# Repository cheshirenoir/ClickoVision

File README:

ClickoVision
A controller replacement for the colecovision.
CC BY SA
See https://ilike8bits.com/introducing-the-clickovision-a-replacement-controller-for-the-colecovision/ for build details and parts.

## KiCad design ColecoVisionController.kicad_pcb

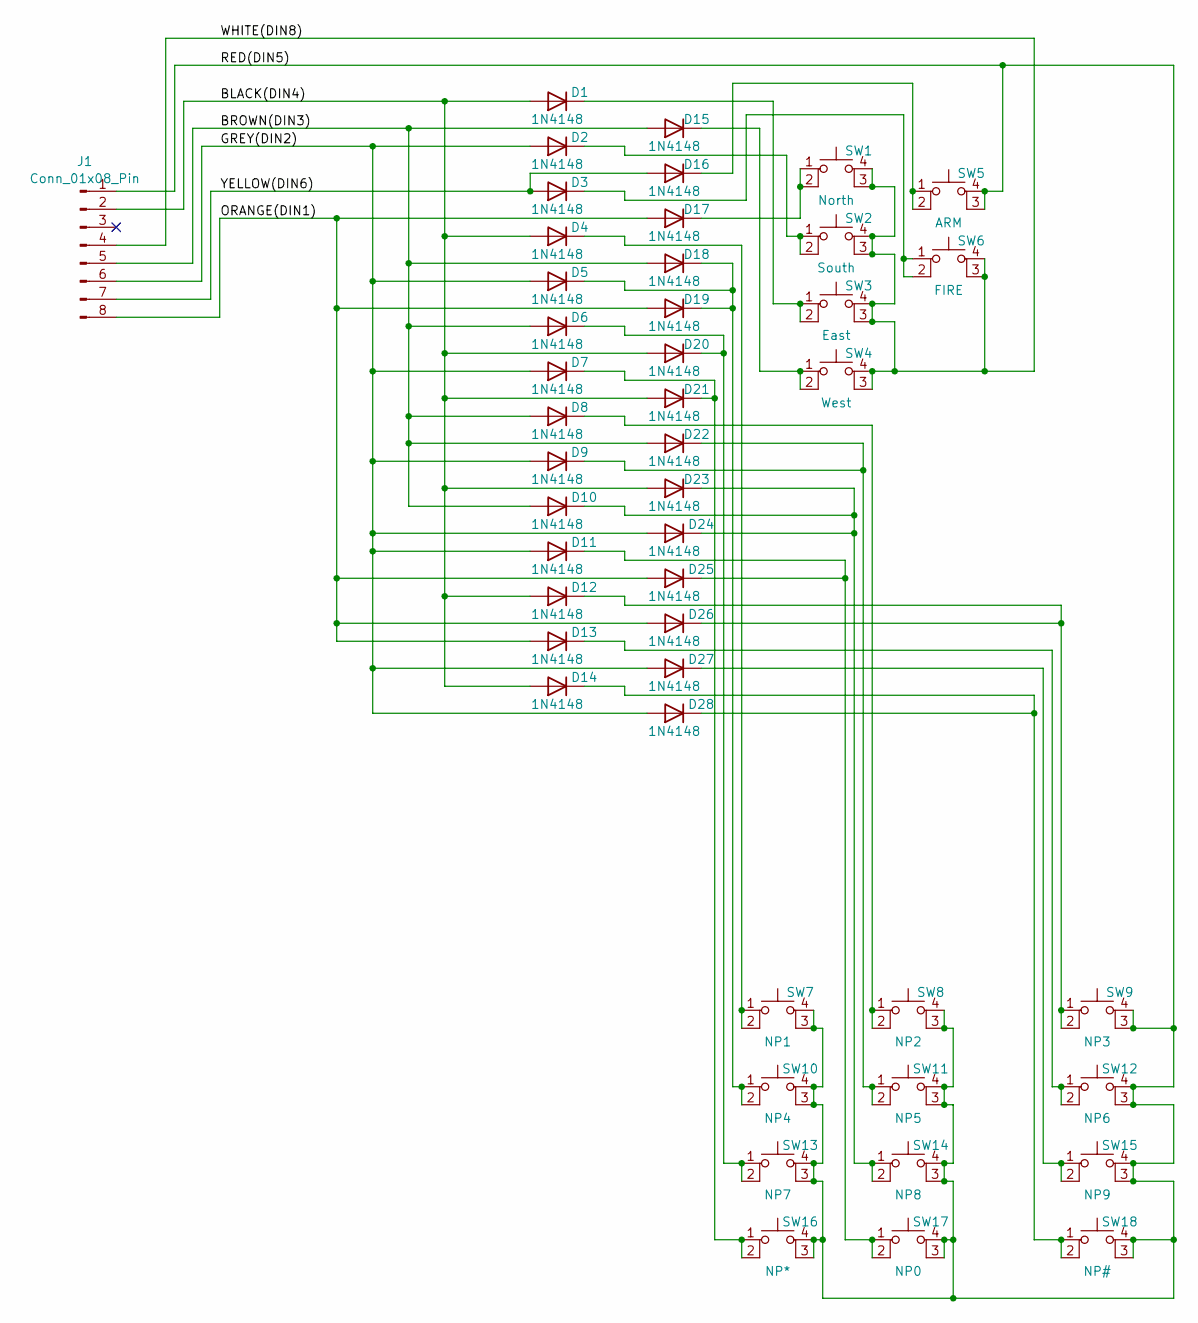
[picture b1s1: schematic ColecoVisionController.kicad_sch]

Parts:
D1, D2, D3, D4, D5, D6, D7, D8, D9, D10, D11, D12, D13, D14, D15, D16, D17, D18, D19, D20, D21, D22, D23, D24, D25, D26, D27, D28: 1N4148; D_MiniMELF_Handsoldering
J1: Conn_01x08_Pin; PinHeader_1x08_P2.54mm_Horizontal
SW1: North; DPadSwitch
SW2: South; DPadSwitch
SW3: East; DPadSwitch
SW4: West; DPadSwitch
SW5: ARM; SnapActionSwitch
SW6: FIRE; SnapActionSwitch
SW7: NP1; SW_PUSH_4pin_6mm
SW8: NP2; SW_PUSH_4pin_6mm
SW9: NP3; SW_PUSH_4pin_6mm
SW10: NP4; SW_PUSH_4pin_6mm
SW11: NP5; SW_PUSH_4pin_6mm
SW12: NP6; SW_PUSH_4pin_6mm
SW13: NP7; SW_PUSH_4pin_6mm
SW14: NP8; SW_PUSH_4pin_6mm
SW15: NP9; SW_PUSH_4pin_6mm
SW16: NP*; SW_PUSH_4pin_6mm
SW17: NP0; SW_PUSH_4pin_6mm
SW18: NP#; SW_PUSH_4pin_6mm

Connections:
/BLACK(DIN4): D1.2 (A), D4.2 (A), D12.2 (A), D14.2 (A), D20.2 (A), D21.2 (A), D23.2 (A), J1.2
/BROWN(DIN3): D6.2 (A), D8.2 (A), D10.2 (A), D15.2 (A), D18.2 (A), D22.2 (A), J1.5
/GREY(DIN2): D2.2 (A), D5.2 (A), D7.2 (A), D9.2 (A), D11.2 (A), D24.2 (A), D27.2 (A), D28.2 (A), J1.6
/ORANGE(DIN1): D13.2 (A), D17.2 (A), D19.2 (A), D25.2 (A), D26.2 (A), J1.8
/RED(DIN5): J1.1, SW5.3 (K), SW5.4 (A), SW7.3 (K), SW7.4 (A), SW8.3 (K), SW8.4 (A), SW9.3 (K), SW9.4 (A), SW10.3 (K), SW10.4 (A), SW11.3 (K), SW11.4 (A), SW12.3 (K), SW12.4 (A), SW13.3 (K), SW13.4 (A), SW14.3 (K), SW14.4 (A), SW15.3 (K), SW15.4 (A), SW16.3 (K), SW16.4 (A), SW17.3 (K), SW17.4 (A), SW18.3 (K), SW18.4 (A)
/WHITE(DIN8): J1.4, SW1.3 (K), SW1.4 (A), SW2.3 (K), SW2.4 (A), SW3.3 (K), SW3.4 (A), SW4.3 (K), SW4.4 (A), SW6.3 (K), SW6.4 (A)
/YELLOW(DIN6): D3.2 (A), D16.2 (A), J1.7
unnamed: D1.1 (K), SW3.1, SW3.2
unnamed: D2.1 (K), SW2.1, SW2.2
unnamed: D3.1 (K), SW6.1, SW6.2
unnamed: D4.1 (K), SW7.1, SW7.2
unnamed: D8.1 (K), SW8.1, SW8.2
unnamed: D10.1 (K), D23.1 (K), D24.1 (K), SW14.1, SW14.2
unnamed: D11.1 (K), D25.1 (K), SW17.1, SW17.2
unnamed: D12.1 (K), D26.1 (K), SW9.1, SW9.2
unnamed: D13.1 (K), SW12.1, SW12.2
unnamed: D14.1 (K), D28.1 (K), SW18.1, SW18.2
unnamed: D15.1 (K), SW4.1, SW4.2
unnamed: D16.1 (K), SW5.1, SW5.2
unnamed: D17.1 (K), SW1.1, SW1.2
unnamed: D5.1 (K), D18.1 (K), D19.1 (K), SW10.1, SW10.2
unnamed: D6.1 (K), D20.1 (K), SW13.1, SW13.2
unnamed: D7.1 (K), D21.1 (K), SW16.1, SW16.2
unnamed: D9.1 (K), D22.1 (K), SW11.1, SW11.2
unnamed: D27.1 (K), SW15.1, SW15.2

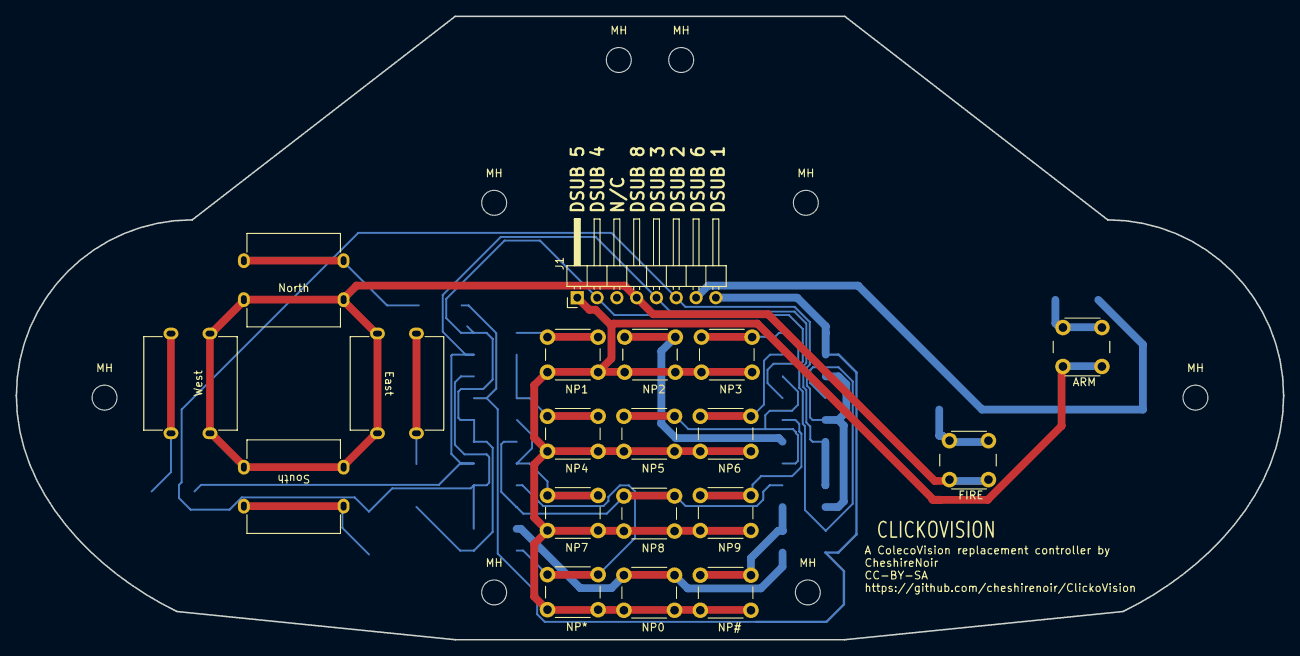
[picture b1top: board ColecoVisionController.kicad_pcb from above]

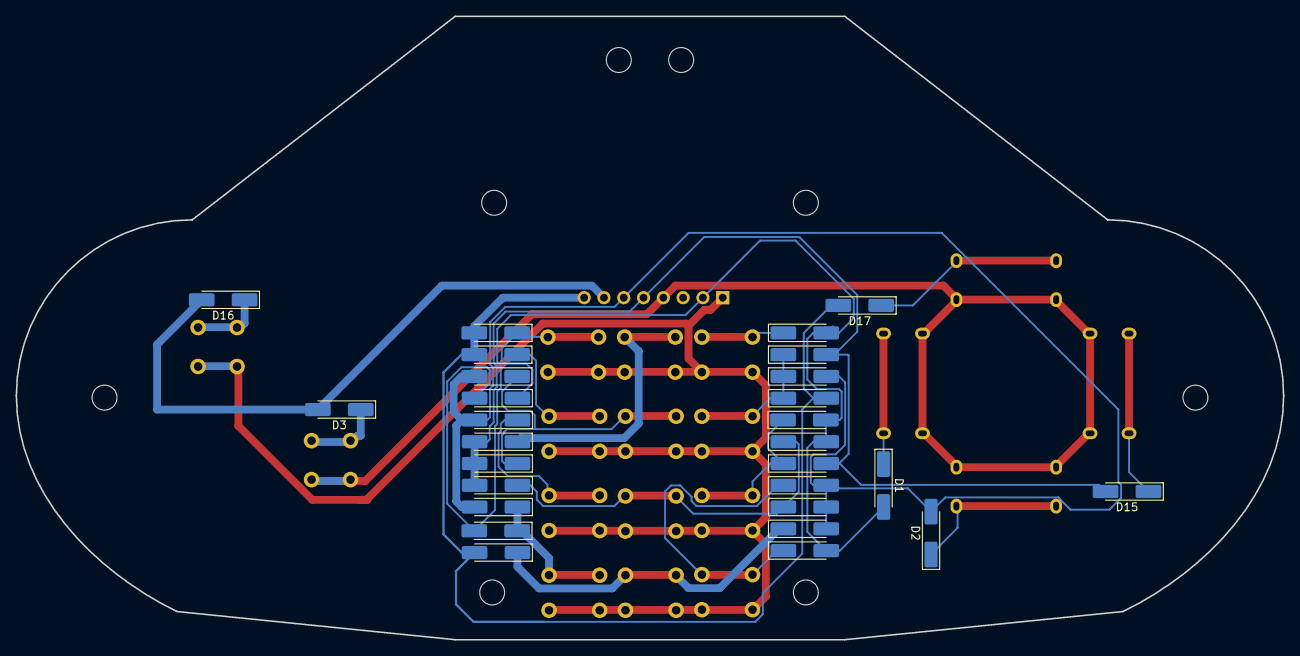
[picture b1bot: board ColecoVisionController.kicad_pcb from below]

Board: 2 copper layers, 162.6 x 80.0 mm, 55 parts (28 on the bottom side), 25 nets.

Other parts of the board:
MH: M3; MountingHole_3.2mm_M3_DIN965
MH#2, MH#3, MH#4, MH#5, MH#6, MH#7, MH#8: M3; MountingHole_3.2mm_M3_DIN965

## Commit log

2024-09-28 Add files via upload
    Initial commit
2024-10-27 Add files via upload
    Updated version with new footprint.
2024-10-27 Delete GERBERSv2 directory
    No longer needed
2024-10-27 Add files via upload
    Revised version of the Gerbers
2024-10-27 Add files via upload
    Custom footprints
2024-10-27 Add files via upload
    Top and bottom panels for the controller
